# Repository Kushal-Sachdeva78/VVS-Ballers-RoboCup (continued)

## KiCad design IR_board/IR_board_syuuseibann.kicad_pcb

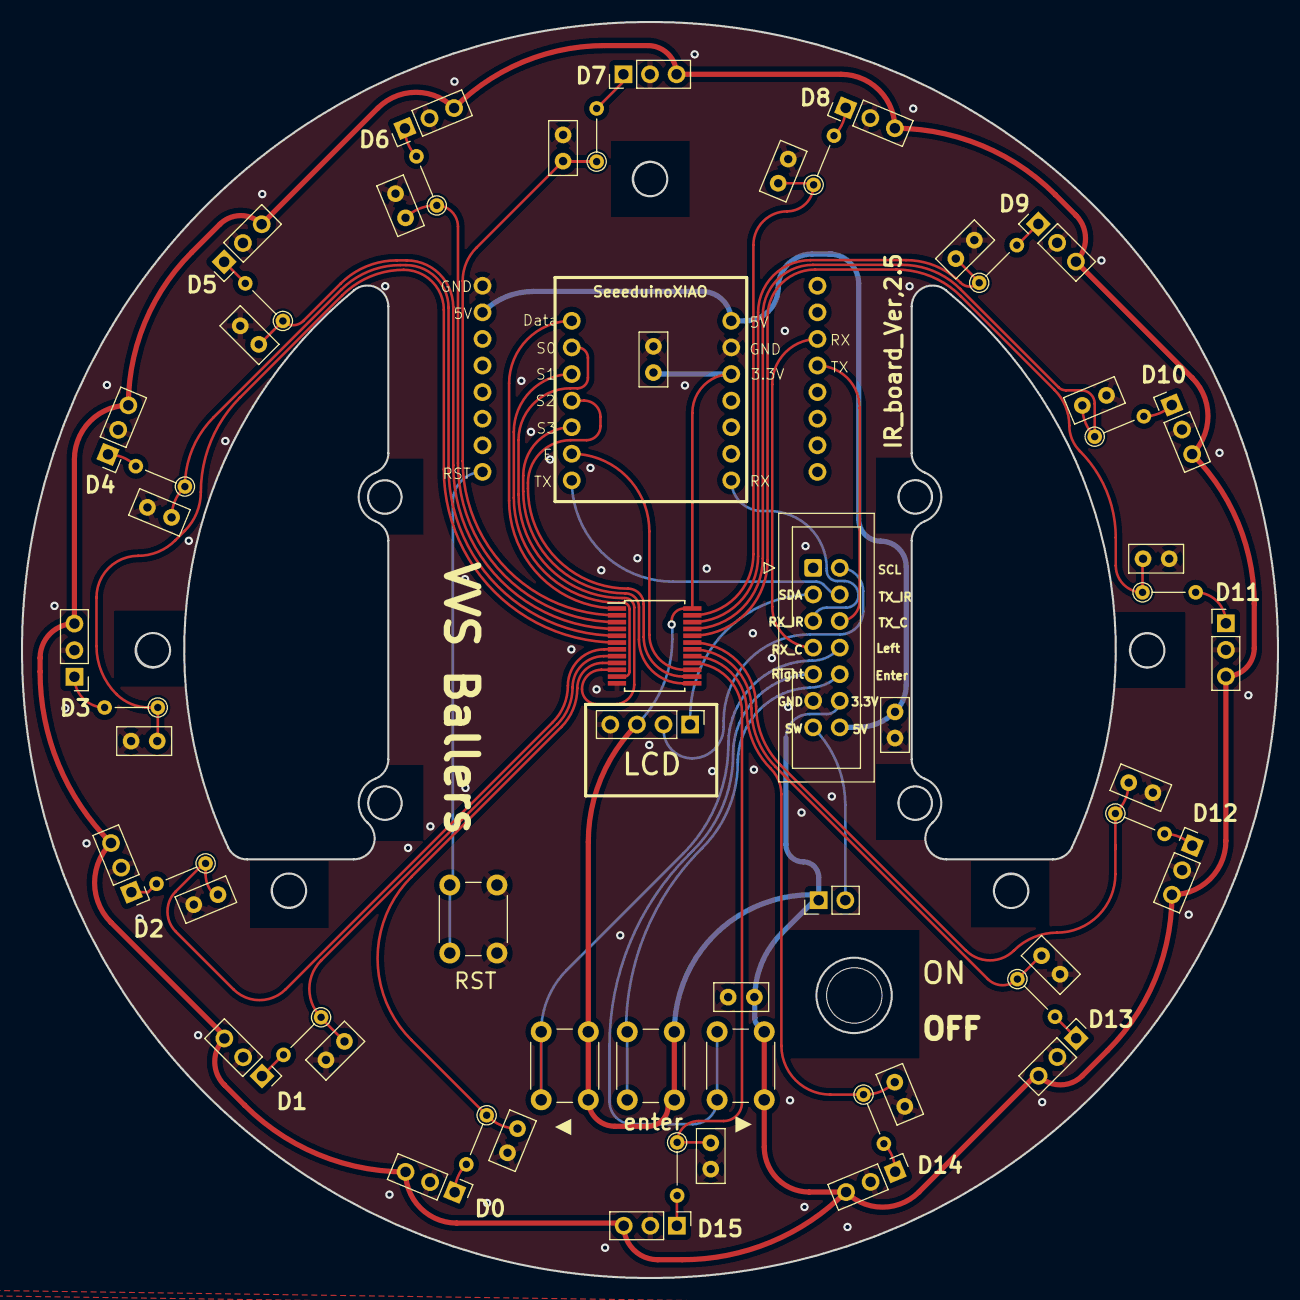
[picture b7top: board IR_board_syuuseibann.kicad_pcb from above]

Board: 2 copper layers, 120.0 x 120.0 mm, 61 parts (0 on the bottom side), 52 nets.

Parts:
C1, C2, C3, C4, C5, C6, C7, C8, C9, C10, C11, C12, C13, C14, C15, C16: 104; C_Disc_D5.0mm_W2.5mm_P2.50mm
C17, C18, C19: C; C_Disc_D5.0mm_W2.5mm_P2.50mm
J1: Conn_01x04_Socket; PinHeader_1x04_P2.54mm_Vertical
J2: Conn_02x07_Top_Bottom; IDC-Header_2x07_P2.54mm_Vertical
R1, R2, R3, R4, R5, R6, R7, R8, R9, R10, R11, R12, R13, R14, R15, R16: 22k; R_Axial_DIN0204_L3.6mm_D1.6mm_P5.08mm_Vertical
RST: SW_DIP_x01; SW_PUSH_6mm_H5mm
SW3: LCD; SW_PUSH_6mm_H5mm
SW4: SW_DIP_x01; PinHeader_1x02_P2.54mm_Vertical
U1: SeeeduinoXIAO; seeeduinoXIAO
U2, U3, U4, U5, U6, U7, U8, U9, U10, U11, U12, U13, U14, U15, U16, U17: TSSP58038; PinHeader_1x03_P2.54mm_Vertical
U18: CD74HC4067SM; SSOP-24_5.3x8.2mm_P0.65mm
U19: open_mv; OpenMV
enter: LCD; SW_PUSH_6mm_H5mm
▶: LCD; SW_PUSH_6mm_H5mm

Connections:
+3.3V: C18.2, C19.2, J1.3, J2.12, SW3.2, SW4.1, U1.12 (3V3), U2.3 (Vin), U3.3 (Vin), U4.3 (Vin), U5.3 (Vin), U6.3 (Vin), U7.3 (Vin), U8.3 (Vin), U9.3 (Vin), U10.3 (Vin), U11.3 (Vin), U12.3 (Vin), U13.3 (Vin), U14.3 (Vin), U15.3 (Vin), U16.3 (Vin), U17.3 (Vin), U18.24 (VCC), enter.2, ▶.2
+5V: C17.1, J2.14, U1.14 (5V), U19.15 (vin)
D0: C3.1, R3.1, U18.9 (I0)
D1: C4.1, R4.1, U18.8 (I1)
D2: C1.1, R1.1, U18.7 (I2)
D3: C2.1, R2.1, U18.6 (I3)
D4: C5.1, R5.1, U18.5 (I4)
D5: C6.1, R6.1, U18.4 (I5)
D6: C7.1, R7.1, U18.3 (I6)
D7: C8.1, R8.1, U18.2 (I7)
D8: C11.1, R11.1, U18.23 (I8)
D9: C12.1, R12.1, U18.22 (I9)
D10: C9.1, R9.1, U18.21 (I10)
D11: C10.1, R10.1, U18.20 (I11)
D12: C13.1, R13.1, U18.19 (I12)
D13: C14.1, R14.1, U18.18 (I13)
D14: C15.1, R15.1, U18.17 (I14)
D15: C16.1, R16.1, U18.16 (I15)
Data_IR_sensor: U1.1 (PA02_A0_D0), U18.1 (COM)
E: U1.6 (PA9_A5_D5_SCL), U18.15 (~E)
GND: C1.2, C2.2, C3.2, C4.2, C5.2, C6.2, C7.2, C8.2, C9.2, C10.2, C11.2, C12.2, C13.2, C14.2, C15.2, C16.2, C17.2, C18.1, C19.1, J1.4, J2.11, RST.2, U1.13 (GND), U2.2 (GND), U3.2 (GND), U4.2 (GND), U5.2 (GND), U6.2 (GND), U7.2 (GND), U8.2 (GND), U9.2 (GND), U10.2 (GND), U11.2 (GND), U12.2 (GND), U13.2 (GND), U14.2 (GND), U15.2 (GND), U16.2 (GND), U17.2 (GND), U18.12 (GND), U19.16 (GND)
IRout0: R3.2, U2.1 (OUT)
IRout1: R4.2, U3.1 (OUT)
IRout2: R1.2, U4.1 (OUT)
IRout3: R2.2, U5.1 (OUT)
IRout4: R5.2, U6.1 (OUT)
IRout5: R6.2, U7.1 (OUT)
IRout6: R7.2, U8.1 (OUT)
IRout7: R8.2, U9.1 (OUT)
IRout8: R11.2, U10.1 (OUT)
IRout9: R12.2, U11.1 (OUT)
IRout10: R9.2, U12.1 (OUT)
IRout11: R10.2, U13.1 (OUT)
IRout12: R13.2, U14.1 (OUT)
IRout13: R14.2, U15.1 (OUT)
IRout14: R15.2, U16.1 (OUT)
IRout15: R16.2, U17.1 (OUT)
LCD-TeensyD10: J2.8, ▶.1
LCD-TeensyD11: J2.9, SW3.1
LCD-TeensyD12: J2.10, enter.1
RST: RST.1, U19.9 (rst)
RX_Boll: J2.5, U1.8 (PB09_A7_D7_RX)
RX_camera: J2.7, U19.6 (rxd/sca)
S0: U1.2 (PA4_A1_D1), U18.10 (S0)
S1: U1.3 (PA10_A2_D2), U18.11 (S1)
S2: U1.4 (PA11_A3_D3), U18.14 (S2)
S3: U1.5 (PA8_A4_D4_SDA), U18.13 (S3)
SCL_LCD: J1.2, J2.2
SDA_LCD: J1.1, J2.3
TX_Boll: J2.4, U1.7 (PB08_A6_D6_TX)
TX_camera: J2.6, U19.5 (txo/scl)
switch: J2.13, SW4.2

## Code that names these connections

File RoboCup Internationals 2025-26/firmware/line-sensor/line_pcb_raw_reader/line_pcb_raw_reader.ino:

/*
  Line PCB — QTR-MD-05A raw reflectance reader (Teensy 4.1)
  ---------------------------------------------------------
  Streams the raw ADC value of all 18 connected sensors so you can
  watch the numbers and learn which reading is "white" on your surface.

  Wiring (from your PCB doc):
    Emitter control CTRL_ODD (shared by all 4 boards) .... Teensy D6
    QTR1 OUT0..OUT4 .................................. A0  A1  A2  A3  A4
    QTR2 OUT0..OUT4 .................................. A5  A6  A7  A8  A9
    QTR3 OUT0..OUT4 .................................. A10 A11 A12 A13 A14
    QTR4 OUT1 OUT2 OUT3  (OUT0 & OUT4 = NC) .......... A15 A16 A17
    Sensors on 3.3V, Teensy on 5V (VIN), common ground.

  ADC: 12-bit -> values range 0..4095.
  No library needed — this is just analogRead().

  Note: analogReadAveraging() and analogReadResolution() are Teensy
  (Teensyduino) functions. Keep this on the Teensy 4.1.
*/

const int EMITTER_PIN = 6;                 // CTRL_ODD shared line
const int NUM_SENSORS = 18;

const int ADC_BITS = 12;                   // 12-bit -> 0..4095
const int ADC_MAX  = (1 << ADC_BITS) - 1;
const unsigned long PRINT_INTERVAL_MS = 150;
const int HEADER_EVERY = 10;               // reprint column header every N updates

// Analog pins in wiring order (board 1 -> board 4)
const int sensorPins[NUM_SENSORS] = {
  A0,  A1,  A2,  A3,  A4,     // QTR1 OUT0..4
  A5,  A6,  A7,  A8,  A9,     // QTR2 OUT0..4
  A10, A11, A12, A13, A14,    // QTR3 OUT0..4
  A15, A16, A17               // QTR4 OUT1, OUT2, OUT3  (OUT0 & OUT4 not connected)
};

// Labels: Q<board>.<output channel>
const char* sensorNames[NUM_SENSORS] = {
  "Q1.0","Q1.1","Q1.2","Q1.3","Q1.4",
  "Q2.0","Q2.1","Q2.2","Q2.3","Q2.4",
  "Q3.0","Q3.1","Q3.2","Q3.3","Q3.4",
  "Q4.1","Q4.2","Q4.3"
};

int values[NUM_SENSORS];
unsigned long lastPrint = 0;
int updateCount = 0;

// right-justify an integer in a field of the given width
void printPadded(int v, int width) {
  int digits = 1, t = (v < 0) ? -v : v;
  while (t >= 10) { t /= 10; digits++; }
  if (v < 0) digits++;
  for (int i = digits; i < width; i++) Serial.print(' ');
  Serial.print(v);
}

// right-justify a string in a field of the given width
void printStrPadded(const char* s, int width) {
  int len = 0;
  while (s[len] != '\0') len++;
  for (int i = len; i < width; i++) Serial.print(' ');
  Serial.print(s);
}

void printHeader() {
  Serial.println();
  for (int i = 0; i < 6; i++) Serial.print(' ');     // align with row label width
  const char* cols[5] = {"OUT0","OUT1","OUT2","OUT3","OUT4"};
  for (int i = 0; i < 5; i++) { Serial.print("  "); printStrPadded(cols[i], 5); }
  Serial.println();
}

// print one board row: label + 5 columns (idx start..start+4)
void printBoardRow(const char* label, int start) {
  printStrPadded(label, 6);
  for (int i = start; i < start + 5; i++) { Serial.print("  "); printPadded(values[i], 5); }
  Serial.println();
}

void setup() {
  Serial.begin(115200);
  while (!Serial && millis() < 3000) { /* wait briefly for USB serial monitor */ }

  analogReadResolution(ADC_BITS);
  analogReadAveraging(16);            // smooth out noise for cleaner readings

  pinMode(EMITTER_PIN, OUTPUT);
  digitalWrite(EMITTER_PIN, HIGH);   // emitters ON

  Serial.println("QTR-MD-05A raw reader ready.");
  Serial.print("ADC range: 0 to "); Serial.println(ADC_MAX);
  Serial.println("Slide a white surface and a dark surface under each sensor and watch the numbers.");
}

void loop() {
  if (millis() - lastPrint < PRINT_INTERVAL_MS) return;
  lastPrint = millis();

  // read every sensor
  for (int i = 0; i < NUM_SENSORS; i++) values[i] = analogRead(sensorPins[i]);

  if (updateCount % HEADER_EVERY == 0) printHeader();
  updateCount++;

  printBoardRow("QTR1:", 0);
  printBoardRow("QTR2:", 5);
  printBoardRow("QTR3:", 10);

  // QTR4: OUT0 and OUT4 are NC -> print "--" so the columns stay aligned
  printStrPadded("QTR4:", 6);
  Serial.print("  "); printStrPadded("--", 5);     // OUT0 (NC)
  Serial.print("  "); printPadded(values[15], 5);  // OUT1
  Serial.print("  "); printPadded(values[16], 5);  // OUT2
  Serial.print("  "); printPadded(values[17], 5);  // OUT3
  Serial.print("  "); printStrPadded("--", 5);     // OUT4 (NC)
  Serial.println();

  // quick min/max across all connected sensors (handy for spotting the bright one)
  int minI = 0, maxI = 0;
  for (int i = 1; i < NUM_SENSORS; i++) {
    if (values[i] < values[minI]) minI = i;
    if (values[i] > values[maxI]) maxI = i;
  }
  Serial.print("  min="); printPadded(values[minI], 4);
  Serial.print(" ("); Serial.print(sensorNames[minI]); Serial.print(")");
  Serial.print("   max="); printPadded(values[maxI], 4);
  Serial.print(" ("); Serial.print(sensorNames[maxI]); Serial.println(")");
  Serial.println();
}

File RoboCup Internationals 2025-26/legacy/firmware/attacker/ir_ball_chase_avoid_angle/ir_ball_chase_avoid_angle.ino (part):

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  Wiring (from the Main PCB doc):
    SLEEP -> 6 ;  M1: 2,3 ;  M2: 4,5 ;  M3: 9,10 ;  M4: 11,12
    BNO055 on Wire2: SDA=25, SCL=24, VIN=3.3V
    IR UART       : Serial4  (RX4 = pin 16  <- IR board   TX_IR)
    Ultrasonic PCB: Serial3  (RX3 = pin 15  <- US board   TX_U,  TX3 = pin 14)
    BT telemetry  : Serial2  (TX2 = pin 8   -> HC-05 RXD,  RX2 = pin 7 <- HC-05 TXD)
                              (HC-05 VCC = 5V from VIN; data pins are 3.3V logic)

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// for KICK_COOLDOWN_MS before it can fire again. A hard KICK_MAX_ON_MS guard
// force-releases the coil if it is EVER energised longer than that, whatever the
// state machine does. Pins from the Main PCB doc:
//   HC-SR04   : TRIG = pin 20, ECHO = pin 21   (sensor at 3.3 V, so ECHO is 3.3 V
//               -> safe wired straight to the Teensy, no divider)
//   Relay IN1 : pin 22  -> switches the kicker solenoid
const int CAPTURE_TRIG = 20;
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
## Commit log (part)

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2025-12-02 Add comprehensive repository README
2026-06-27 Add RoboCup Internationals 2025-26: firmware, PCB, CAD, docs
    New season folder alongside Regionals/Nationals. Includes the cleaned
    current firmware (attacker, defender, IR, line, ultrasonic, motor),
    KiCad PCB sources + fab zips, Fusion/print CAD tracked via Git LFS,
    and README plus technical docs. No existing files were changed.
2026-06-28 Normalize names to Title case; reorganize CAD prints by subsystem; add root README + LICENSE
    - Capitalize all category folders (CAD, PCB, Firmware, Docs, Legacy) and their
    subfolders (IR, Main, Line, Power, Ultrasonic, Fusion, Wiring, Fabrication,
    IR_Ball_Sensor, Line_Sensor, Motor_Current); normalize the lowercase Arduino
    sketch folders and their matching .ino files.
    - CAD: rename print/ -> Printable/ and regroup the STLs by subsystem
    (Chassis, Drive, Ball_Capture, Sensor_Mounts).
2026-06-28 Defender line-edge keeper + camera/IR ball fusion; add BOM and block diagram
    Make the firmware match the documented behaviour (close the over-claims):
    - Defender (Defender_Full): decode the real 9-byte A5/5A line mask frame - the same
    one the attacker already uses - instead of the dead 8-byte depth frame nothing
    produced. Standoff now comes from the back ultrasonic (continuous); the FRONT line
    flag is the up-field box-edge limit and RIGHT/LEFT flags are corner limits. The
    LINE_DEPTH_SETPOINT depth contract is removed.
2026-06-28 Add inter-robot role switching (nRF24L01+ RobotLink); tidy IR distance notes
    - Firmware/Comms/RobotLink: an nRF24L01+ (2.4 GHz, peer-to-peer) role-arbitration
    module. One firmware on both robots; partner alive -> play base role, partner
    lost -> cover the goal as keeper. Demote is immediate; promote back waits for a
    referee GO edge (or a timed resume if GO is not wired). Fail-safe: keeper before
    the first heartbeat, and the static base role if the radio is absent. House
    framing reused (2-byte sync + rolling seq + CRC-8 poly 0x07). Uses SPI1
2026-06-28 RobotLink: remove the module-level status caveat wording
    Keep the per-pin >>> BENCH-VERIFY wiring notes and the fail-safe behaviour; only the
    module status lines are removed (RobotLink.h, the Comms README, and the dispatcher
    example).
2026-06-28 RobotMain: combined firmware that runs either role live (RobotLink dispatch)
    One sketch flashed to both robots. RobotMain.ino calls RobotLink.update() each loop and
    runs attackerLoop() or defenderLoop() per the arbitrated role, safe-stopping the outgoing
    role (motors + solenoid) on a switch. The two behaviour bodies are generated from the
    canonical Attacker/Defender sketches into AttackerRole.cpp / DefenderRole.cpp, each wrapped
    in an anonymous namespace so their shared globals and clashing defines stay isolated;
    RobotLink is bundled in the folder. The standalone Attacker/Defender sketches are unchanged
2026-06-28 Close 3 TDP accuracy gaps in the repo: DRVOFF wiring, camera CRC-8, drive normalisation
    1. Motor-current: stale comments said DRVOFF was tied to GND (so the Nano could not coast
    a stalled motor). Updated to the as-built wiring - DRVOFF lifted onto the Nano D2-D5 -
    in both Motor_Current sketches and HOW_IT_WORKS; removed the resolved board-mod caveat.
    2. Camera link now carries a real CRC-8 (poly 0x07) instead of a modular sum: Goal_Cam.py
    and Goal_Cam_Ball.py compute crc8() over the payload, and the attacker camPoll + the
    defender cameraPoll verify it. IR is documented precisely as delimited ASCII with no
